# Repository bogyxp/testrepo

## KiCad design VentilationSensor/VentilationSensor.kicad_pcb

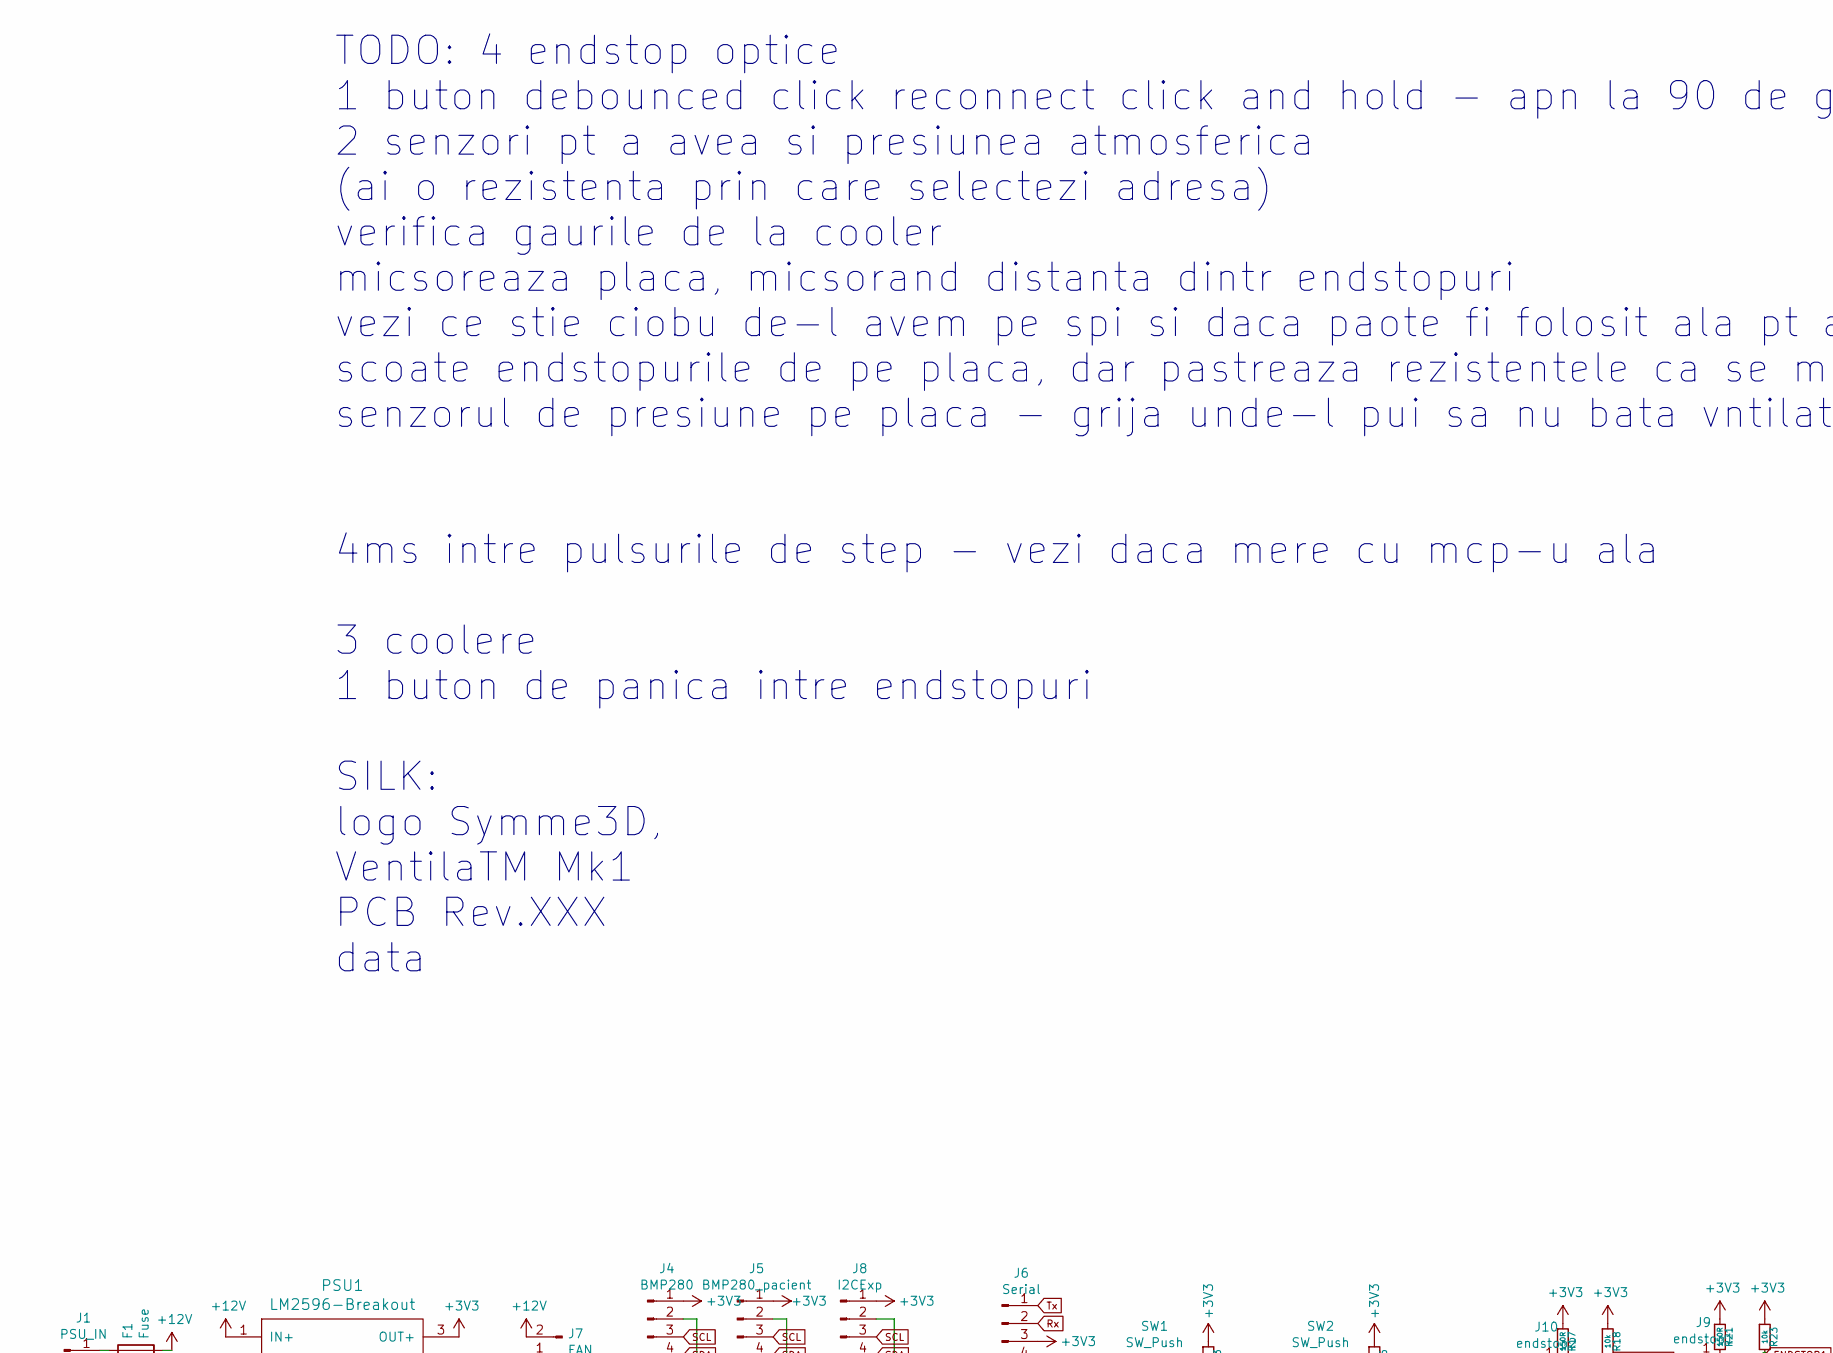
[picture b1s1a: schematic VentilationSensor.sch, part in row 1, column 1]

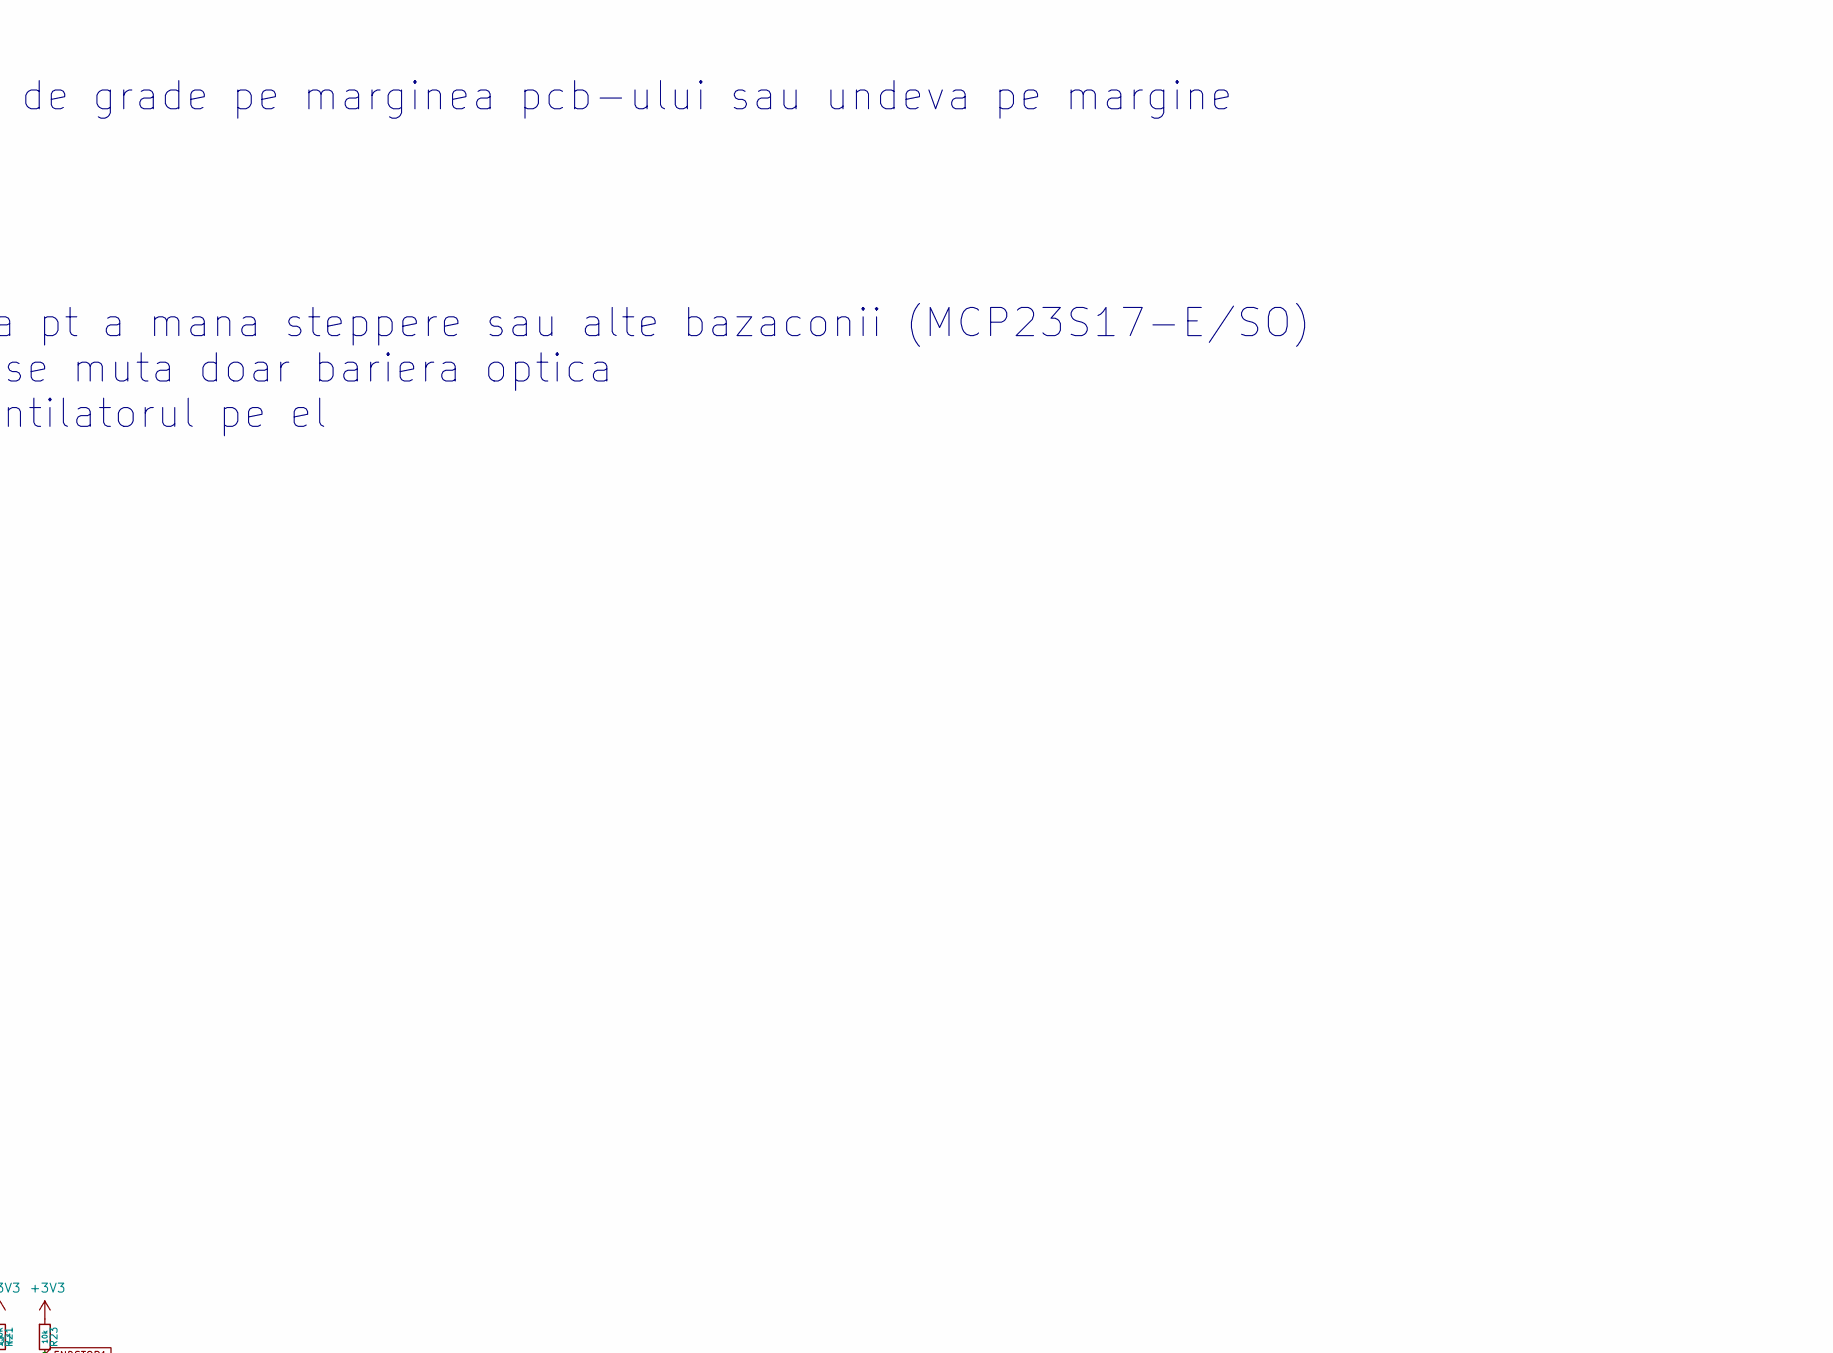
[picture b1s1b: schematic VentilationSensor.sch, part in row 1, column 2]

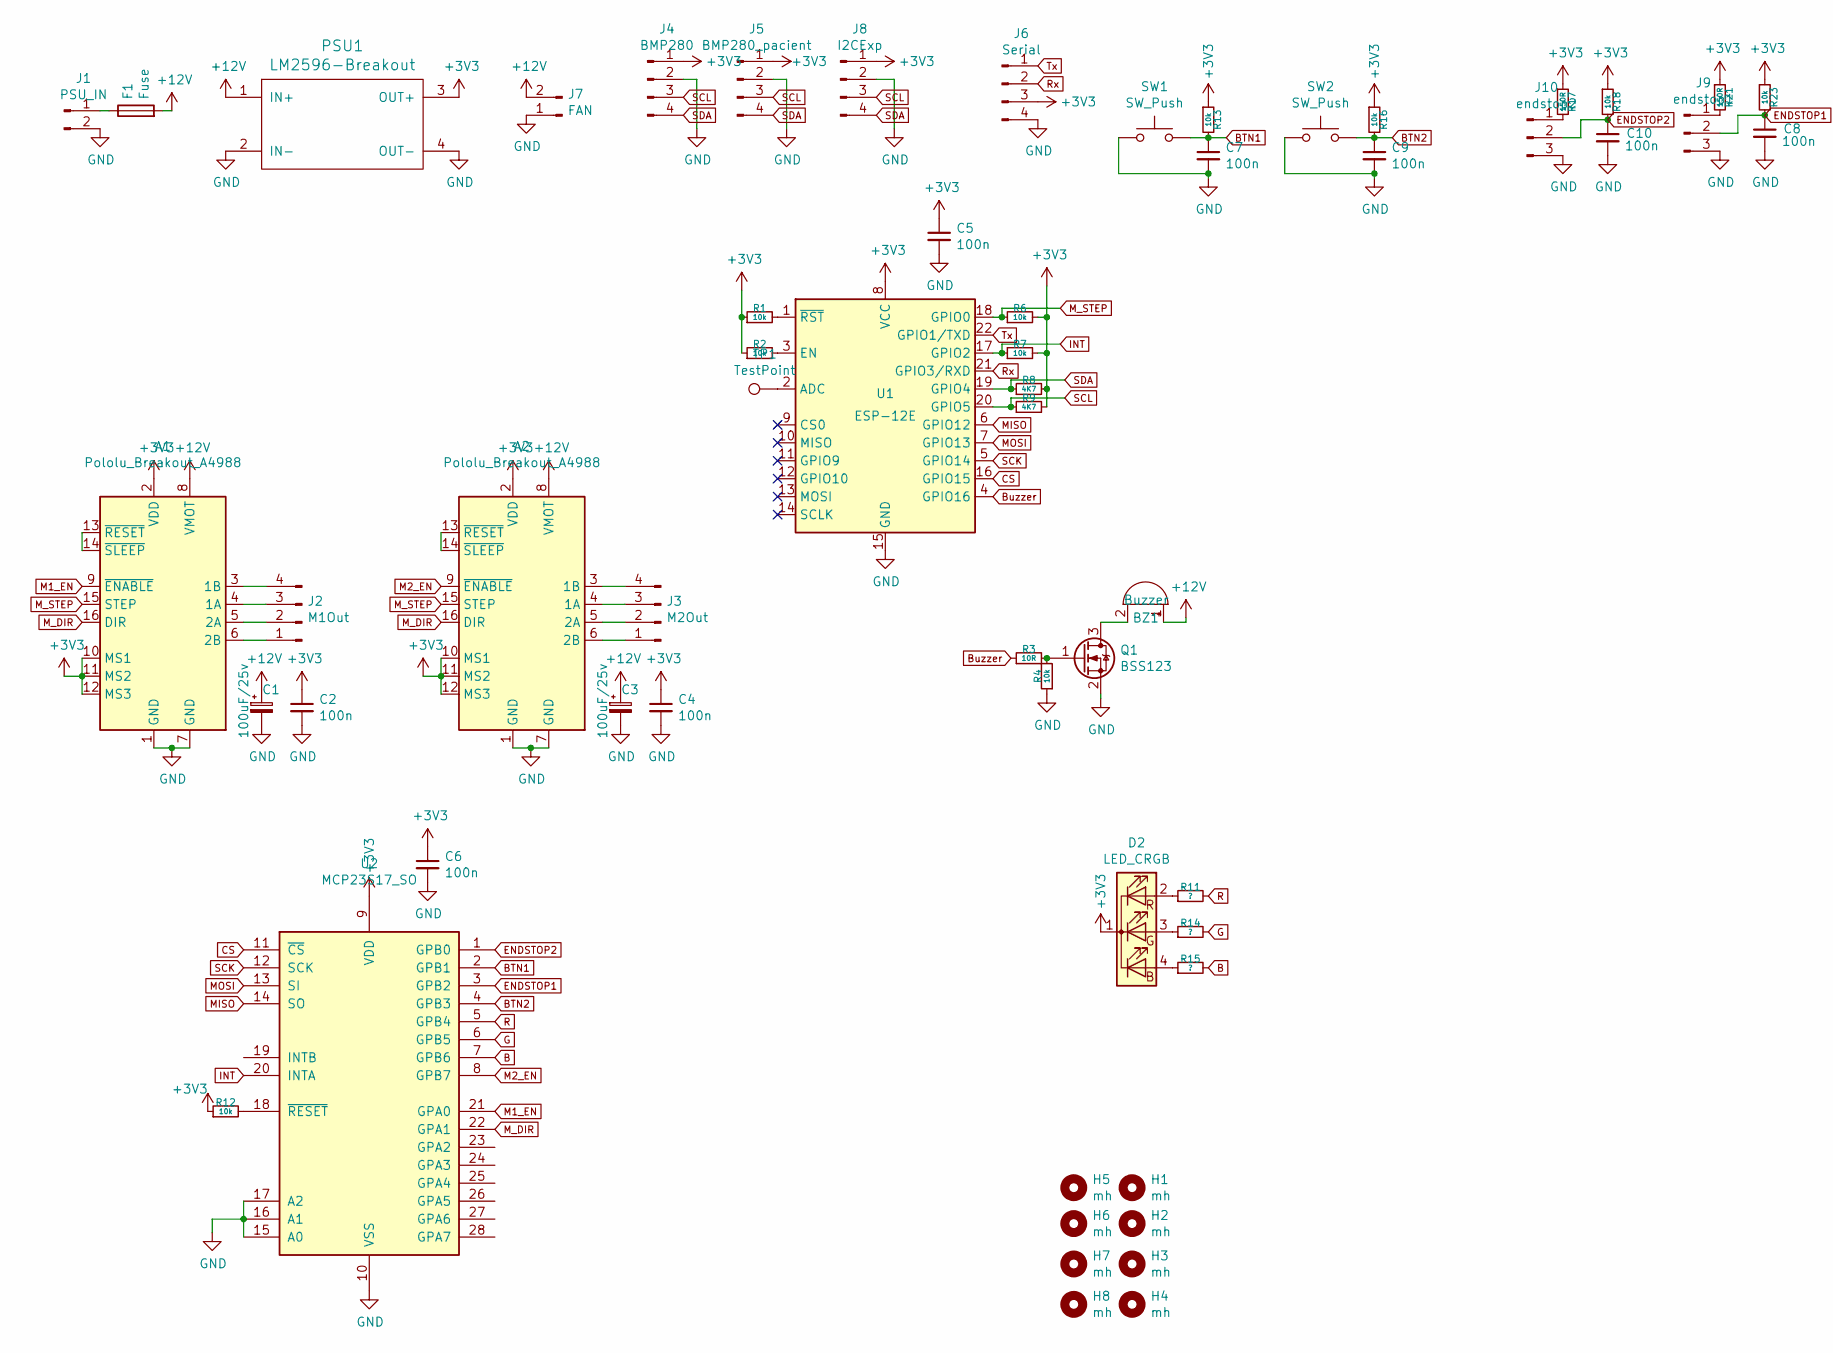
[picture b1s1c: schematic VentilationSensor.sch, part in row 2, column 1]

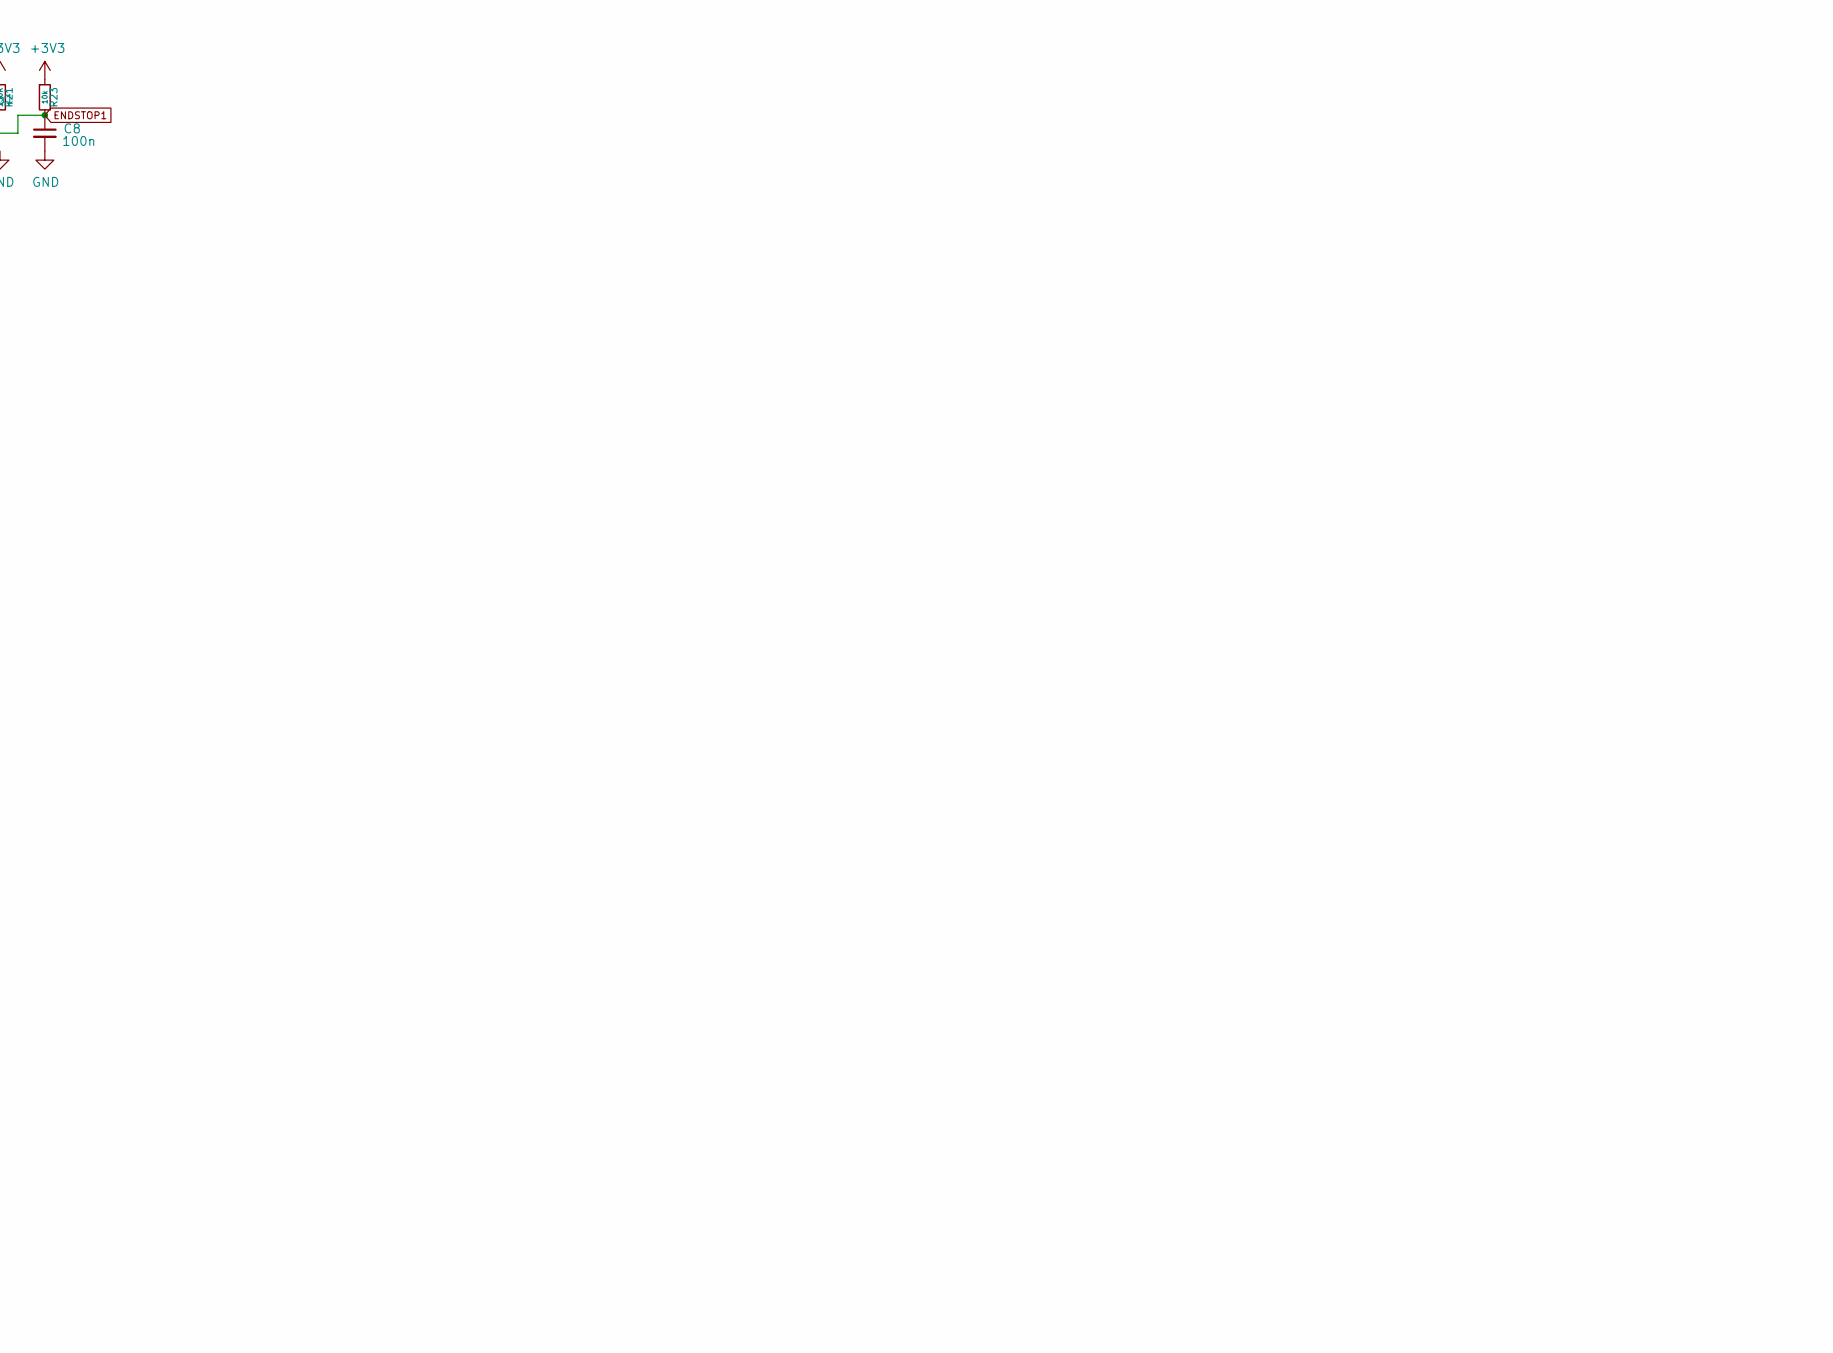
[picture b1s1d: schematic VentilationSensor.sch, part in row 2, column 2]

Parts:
A1, A2: Pololu_Breakout_A4988; Pololu_Breakout-16_15.2x20.3mm
BZ1: Buzzer; Buzzer_12x9.5RM7.6
C1, C3: 100uF/25v; CP_Elec_6.3x7.7
C2, C4, C5, C6, C7, C8, C9, C10: 100n; C_0805_2012Metric_Pad1.15x1.40mm_HandSolder
D2: LED_CRGB; LED_D5.0mm-4_RGB_Wide_Pins
F1: Fuse; Fuse_BelFuse_0ZRE0100FF_L18.7mm_W5.1mm
H1, H2, H3, H4, H5, H6, H7, H8: mh; MountingHole_3.2mm_M3
J1: PSU_IN; TerminalBlock_bornier-2_P5.08mm
J2: M1Out; PinHeader_1x04_P2.54mm_Vertical
J3: M2Out; PinHeader_1x04_P2.54mm_Vertical
J4: BMP280; PinHeader_1x04_P2.54mm_Vertical
J5: BMP280_pacient; PinHeader_1x04_P2.54mm_Vertical
J6: Serial; PinHeader_1x04_P2.54mm_Vertical
J7: FAN; PinHeader_1x02_P2.54mm_Vertical
J8: I2CExp; PinHeader_1x04_P2.54mm_Vertical
J9: endstop1; PinHeader_1x03_P2.54mm_Vertical
J10: endstop2; PinHeader_1x03_P2.54mm_Vertical
PSU1: LM2596-Breakout; LM2596-breakout_board
Q1: BSS123; SOT-23
R1, R2, R4, R6, R7, R12, R13, R16, R18, R23: 10k; R_0805_2012Metric_Pad1.15x1.40mm_HandSolder
R3: 10R; R_0805_2012Metric_Pad1.15x1.40mm_HandSolder
R8, R9: 4K7; R_0805_2012Metric_Pad1.15x1.40mm_HandSolder
R11, R14, R15: ?; R_0805_2012Metric_Pad1.15x1.40mm_HandSolder
R17, R21: 150R; R_0805_2012Metric_Pad1.15x1.40mm_HandSolder
SW1, SW2: SW_Push; SW_PUSH_6mm_H7.3mm
TP1: TestPoint; TestPoint_Pad_D1.5mm
U1: ESP-12E
U2: MCP23S17_SO; SOIC-28W_7.5x17.9mm_P1.27mm

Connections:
+3V3: A1.2 (VDD), A1.10 (MS1), A1.11 (MS2), A1.12 (MS3), A2.2 (VDD), A2.10 (MS1), A2.11 (MS2), A2.12 (MS3), C2.1, C4.1, C5.1, C6.1, D2.1 (K), J4.1, J5.1, J6.3, J8.1, PSU1.3 (OUT+), R1.1, R2.1, R6.2, R7.2, R8.2, R9.2, R12.1, R13.1, R16.1, R17.1, R18.1, R21.1, R23.1, U1.8 (VCC), U2.9 (VDD)
+12V: A1.8 (VMOT), A2.8 (VMOT), BZ1.1 (-), C1.1, C3.1, F1.2, J7.2, PSU1.1 (IN+)
B: R15.2, U2.7 (GPB6)
BTN1: C7.1, R13.2, SW1.2, U2.2 (GPB1)
BTN2: C9.1, R16.2, SW2.2, U2.4 (GPB3)
Buzzer: R3.1, U1.4 (GPIO16)
CS: U1.16 (GPIO15), U2.11 (~CS~)
ENDSTOP1: C8.1, J9.2, R23.2, U2.3 (GPB2)
ENDSTOP2: C10.1, J10.2, R18.2, U2.1 (GPB0)
G: R14.2, U2.6 (GPB5)
GND: A1.1 (GND), A1.7 (GND), A2.1 (GND), A2.7 (GND), C1.2, C2.2, C3.2, C4.2, C5.2, C6.2, C7.2, C8.2, C9.2, C10.2, J1.2, J4.2, J5.2, J6.4, J7.1, J8.2, J9.3, J10.3, PSU1.2 (IN-), PSU1.4 (OUT-), Q1.2 (S), R4.1, SW1.1, SW2.1, U1.15 (GND), U2.10 (VSS), U2.15 (A0), U2.16 (A1), U2.17 (A2)
INT: R7.1, U1.17 (GPIO2), U2.20 (INTA)
M1_EN: A1.9 (~ENABLE), U2.21 (GPA0)
M2_EN: A2.9 (~ENABLE), U2.8 (GPB7)
MISO: U1.6 (GPIO12), U2.14 (SO)
MOSI: U1.7 (GPIO13), U2.13 (SI)
M_DIR: A1.16 (DIR), A2.16 (DIR), U2.22 (GPA1)
M_STEP: A1.15 (STEP), A2.15 (STEP), R6.1, U1.18 (GPIO0)
unnamed: A1.3 (1B), J2.4
unnamed: A1.4 (1A), J2.3
unnamed: A1.5 (2A), J2.2
unnamed: A1.6 (2B), J2.1
unnamed: A1.13 (~RESET), A1.14 (~SLEEP)
unnamed: A2.3 (1B), J3.4
unnamed: A2.4 (1A), J3.3
unnamed: A2.5 (2A), J3.2
unnamed: A2.6 (2B), J3.1
unnamed: A2.13 (~RESET), A2.14 (~SLEEP)
unnamed: BZ1.2 (+), Q1.3 (D)
unnamed: D2.2 (RA), R11.1
unnamed: D2.3 (GA), R14.1
unnamed: D2.4 (BA), R15.1
unnamed: F1.1, J1.1
unnamed: J9.1, R21.2
unnamed: J10.1, R17.2
unnamed: Q1.1 (G), R3.2, R4.2
unnamed: R1.2, U1.1 (~RST)
unnamed: R2.2, U1.3 (EN)
unnamed: R12.2, U2.18 (~RESET~)
unnamed: TP1.1, U1.2 (ADC)
R: R11.2, U2.5 (GPB4)
Rx: J6.2, U1.21 (GPIO3/RXD)
SCK: U1.5 (GPIO14), U2.12 (SCK)
SCL: J4.3, J5.3, J8.3, R9.1, U1.20 (GPIO5)
SDA: J4.4, J5.4, J8.4, R8.1, U1.19 (GPIO4)
Tx: J6.1, U1.22 (GPIO1/TXD)

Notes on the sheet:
TODO: 4 endstop optice 1 buton debounced click reconnect click and hold - apn la 90 de grade pe marginea pcb-ului sau undeva pe margine 2 senzori pt a avea si presiunea atmosferica (ai o rezistenta prin care selectezi adresa) verifica gaurile de la cooler micsoreaza placa, micsorand distanta dintr 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

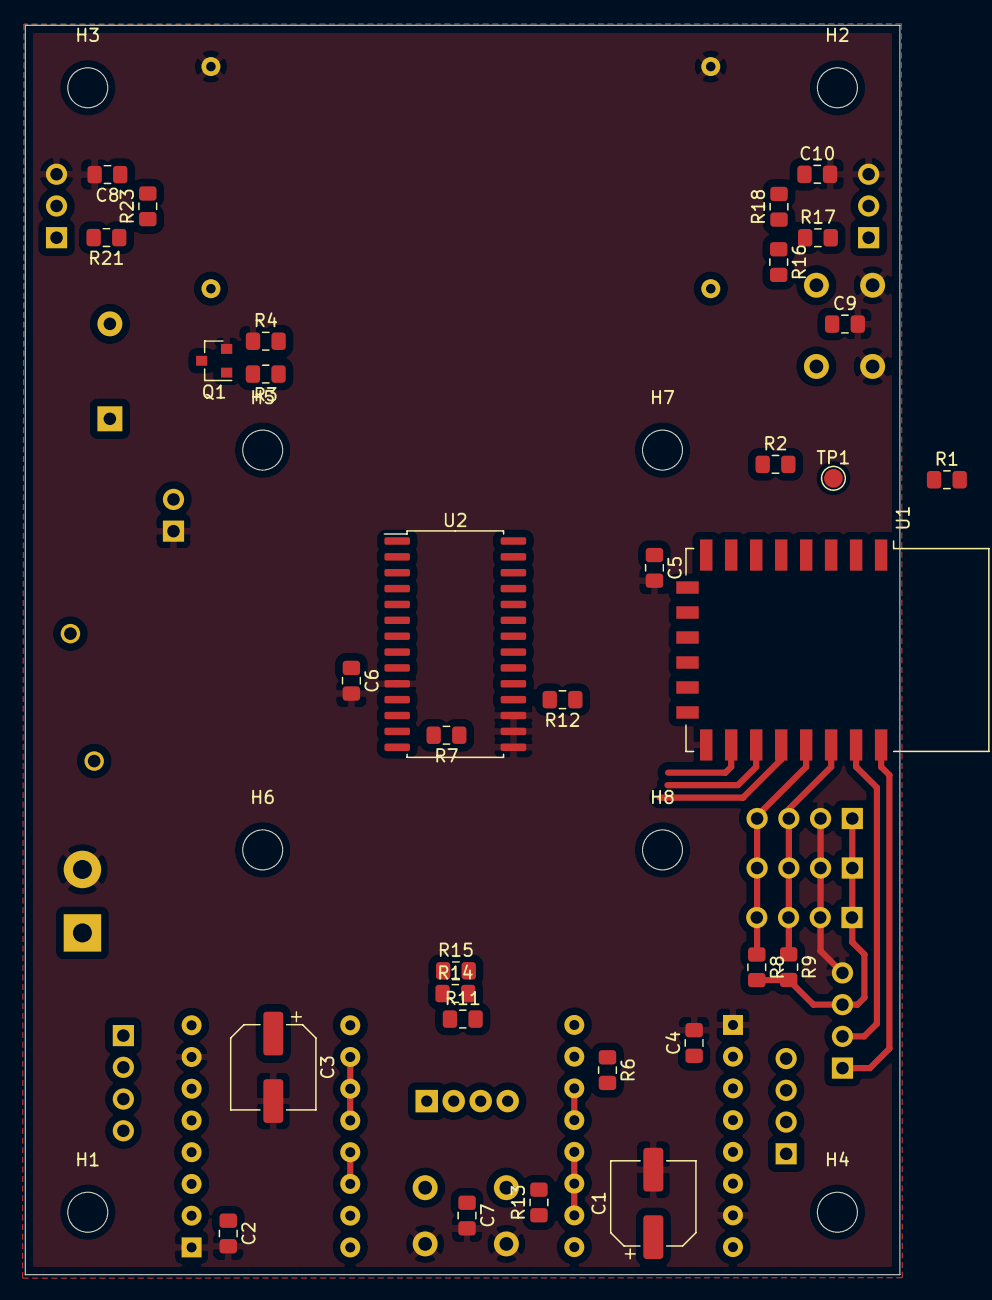
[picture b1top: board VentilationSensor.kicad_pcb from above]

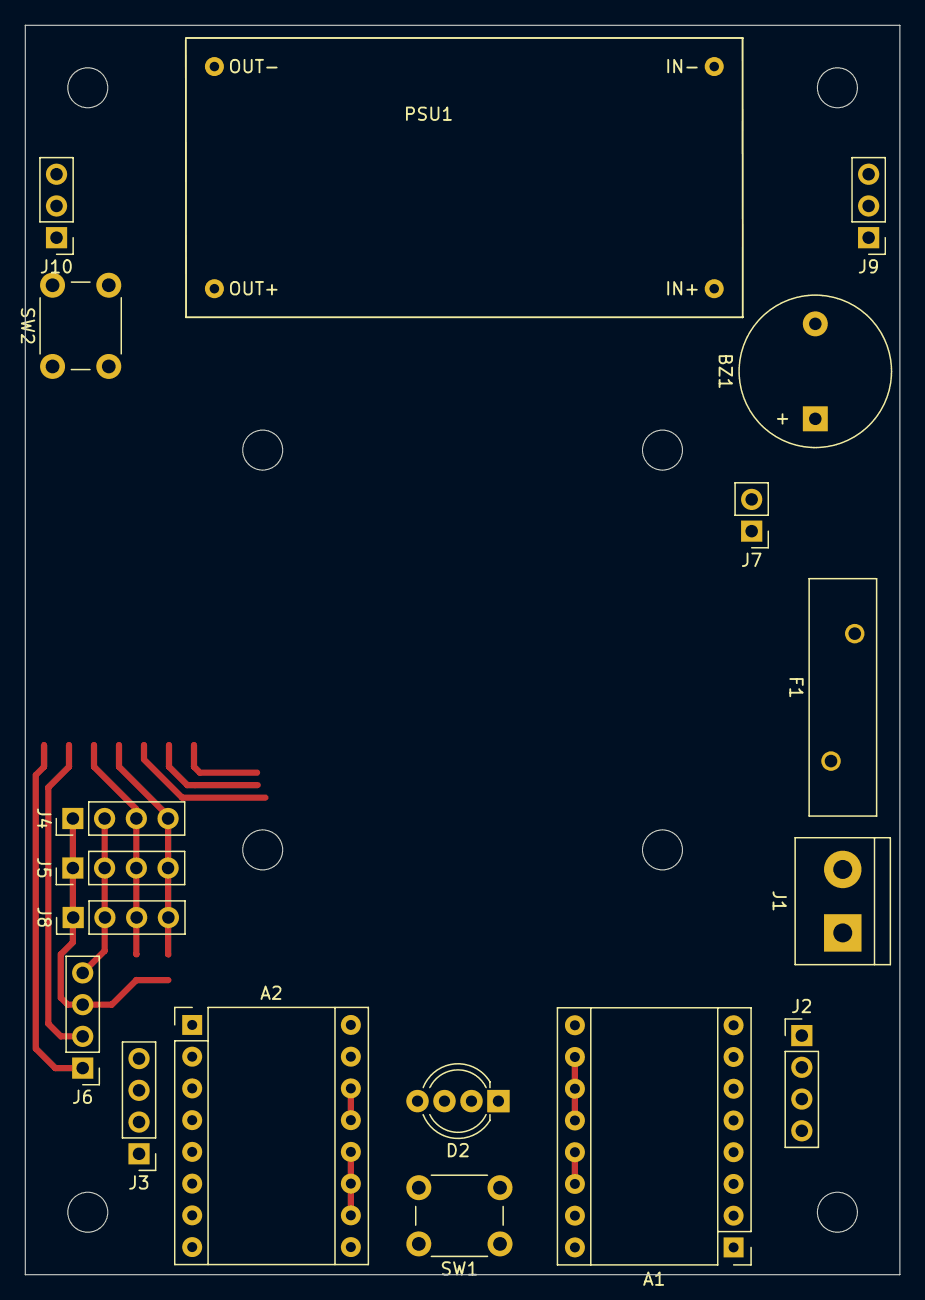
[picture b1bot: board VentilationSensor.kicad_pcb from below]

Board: 2 copper layers, 70.0 x 100.0 mm, 58 parts (18 on the bottom side), 46 nets.
